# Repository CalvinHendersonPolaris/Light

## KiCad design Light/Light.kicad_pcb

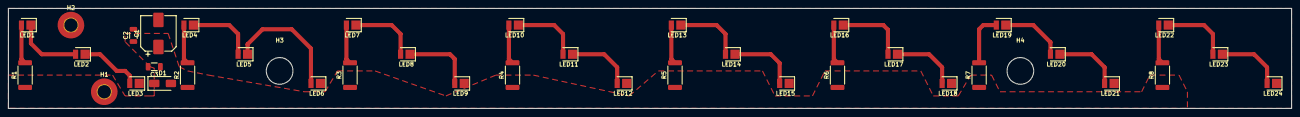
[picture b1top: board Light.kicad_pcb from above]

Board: 2 copper layers, 308.0 x 24.0 mm, 40 parts (0 on the bottom side), 26 nets.

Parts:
C1: 100u; CP_Elec_8x10
C2: 10u; C_1206_3216Metric
C3: 100n; C_1206_3216Metric
D1: SMAJ40CA; D_SMA
H1, H2: MountingHole_Pad_MP; MountingHole_3.2mm_M3_Pad_TopBottom
H3, H4: MountingHole; MountingHole_6.4mm_M6
LED1, LED2, LED3, LED4, LED5, LED6, LED7, LED8, LED9, LED10, LED11, LED12, LED13, LED14, LED15, LED16, LED17, LED18, LED19, LED20, LED21, LED22, LED23, LED24: JB2835BWT-G-U27EA0000-N000P001; LED_PLCC_2835
R1, R2, R3, R4, R5, R6, R7, R8: 100; R_2512_6332Metric

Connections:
/V_Vehicle: C1.1, C2.1, C3.1, D1.2 (A2), R1.1, R2.1, R3.1, R4.1, R5.1, R6.1, R7.1, R8.1
GND: C1.2, C2.2, C3.2, D1.1 (A1), LED3.1, LED6.1, LED9.1, LED12.1, LED15.1, LED18.1, LED21.1, LED24.1
unnamed: LED1.1, LED2.2
unnamed: LED1.2, R1.2
unnamed: LED2.1, LED3.2
unnamed: LED4.1, LED5.2
unnamed: LED4.2, R2.2
unnamed: LED5.1, LED6.2
unnamed: LED7.1, LED8.2
unnamed: LED7.2, R3.2
unnamed: LED8.1, LED9.2
unnamed: LED10.1, LED11.2
unnamed: LED10.2, R4.2
unnamed: LED11.1, LED12.2
unnamed: LED13.1, LED14.2
unnamed: LED13.2, R5.2
unnamed: LED14.1, LED15.2
unnamed: LED16.1, LED17.2
unnamed: LED16.2, R6.2
unnamed: LED17.1, LED18.2
unnamed: LED19.1, LED20.2
unnamed: LED19.2, R7.2
unnamed: LED20.1, LED21.2
unnamed: LED22.1, LED23.2
unnamed: LED22.2, R8.2
unnamed: LED23.1, LED24.2
